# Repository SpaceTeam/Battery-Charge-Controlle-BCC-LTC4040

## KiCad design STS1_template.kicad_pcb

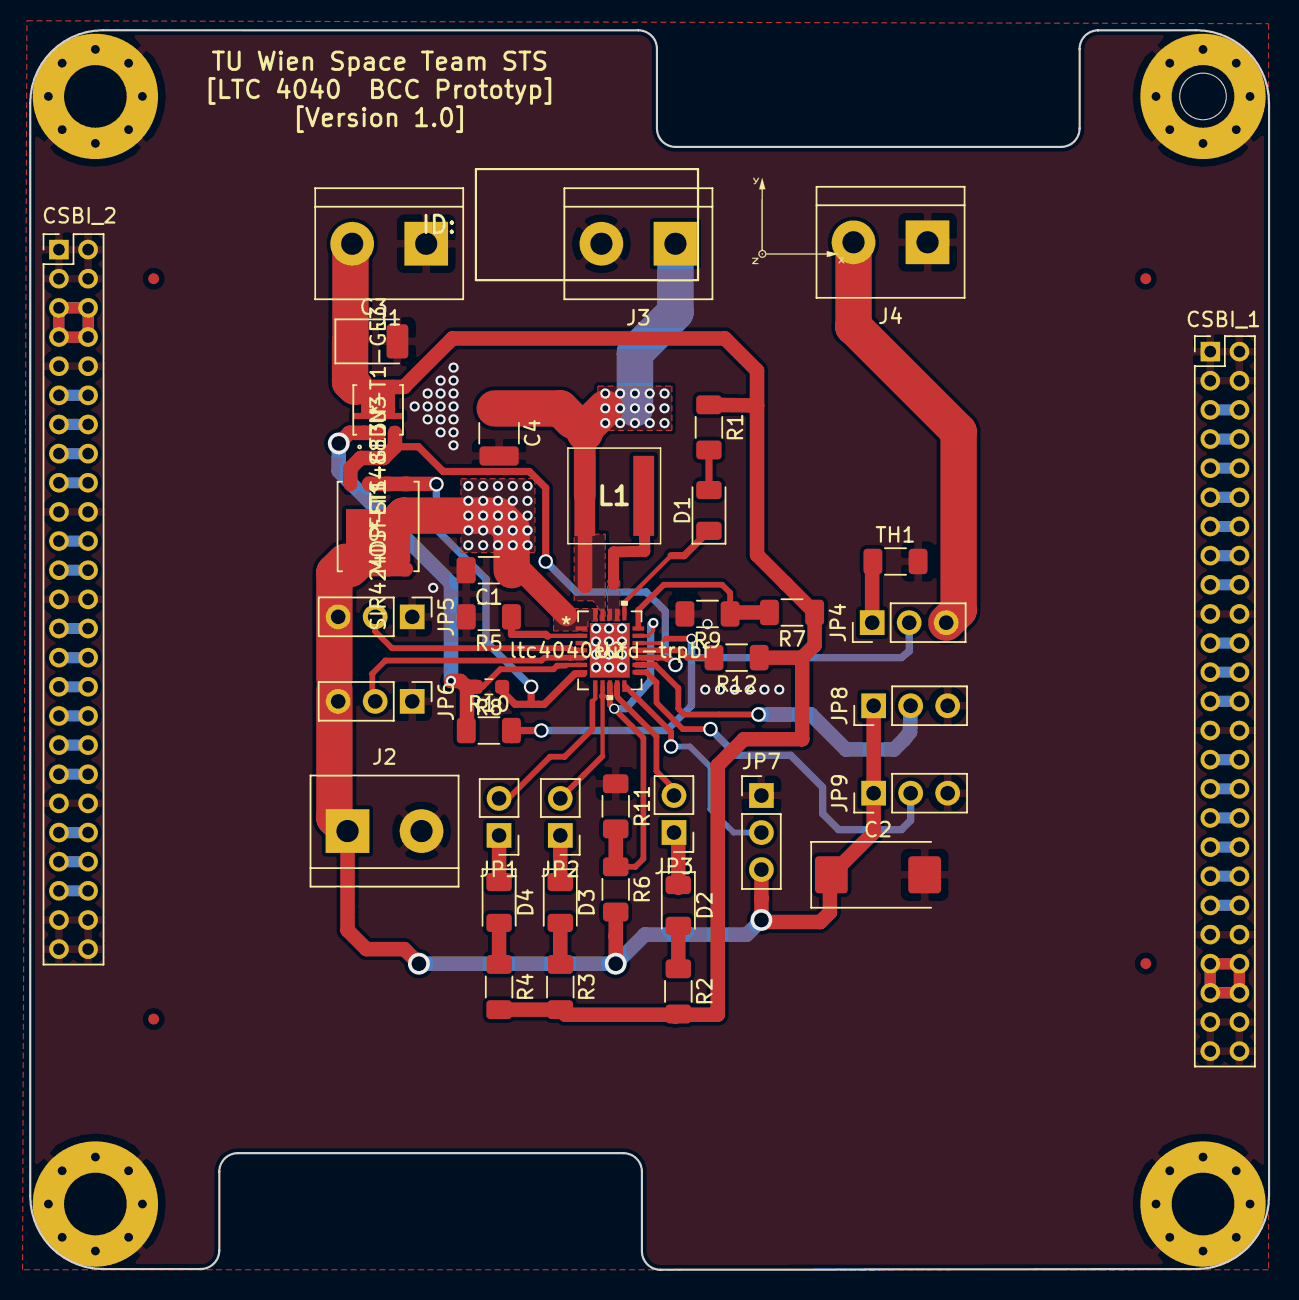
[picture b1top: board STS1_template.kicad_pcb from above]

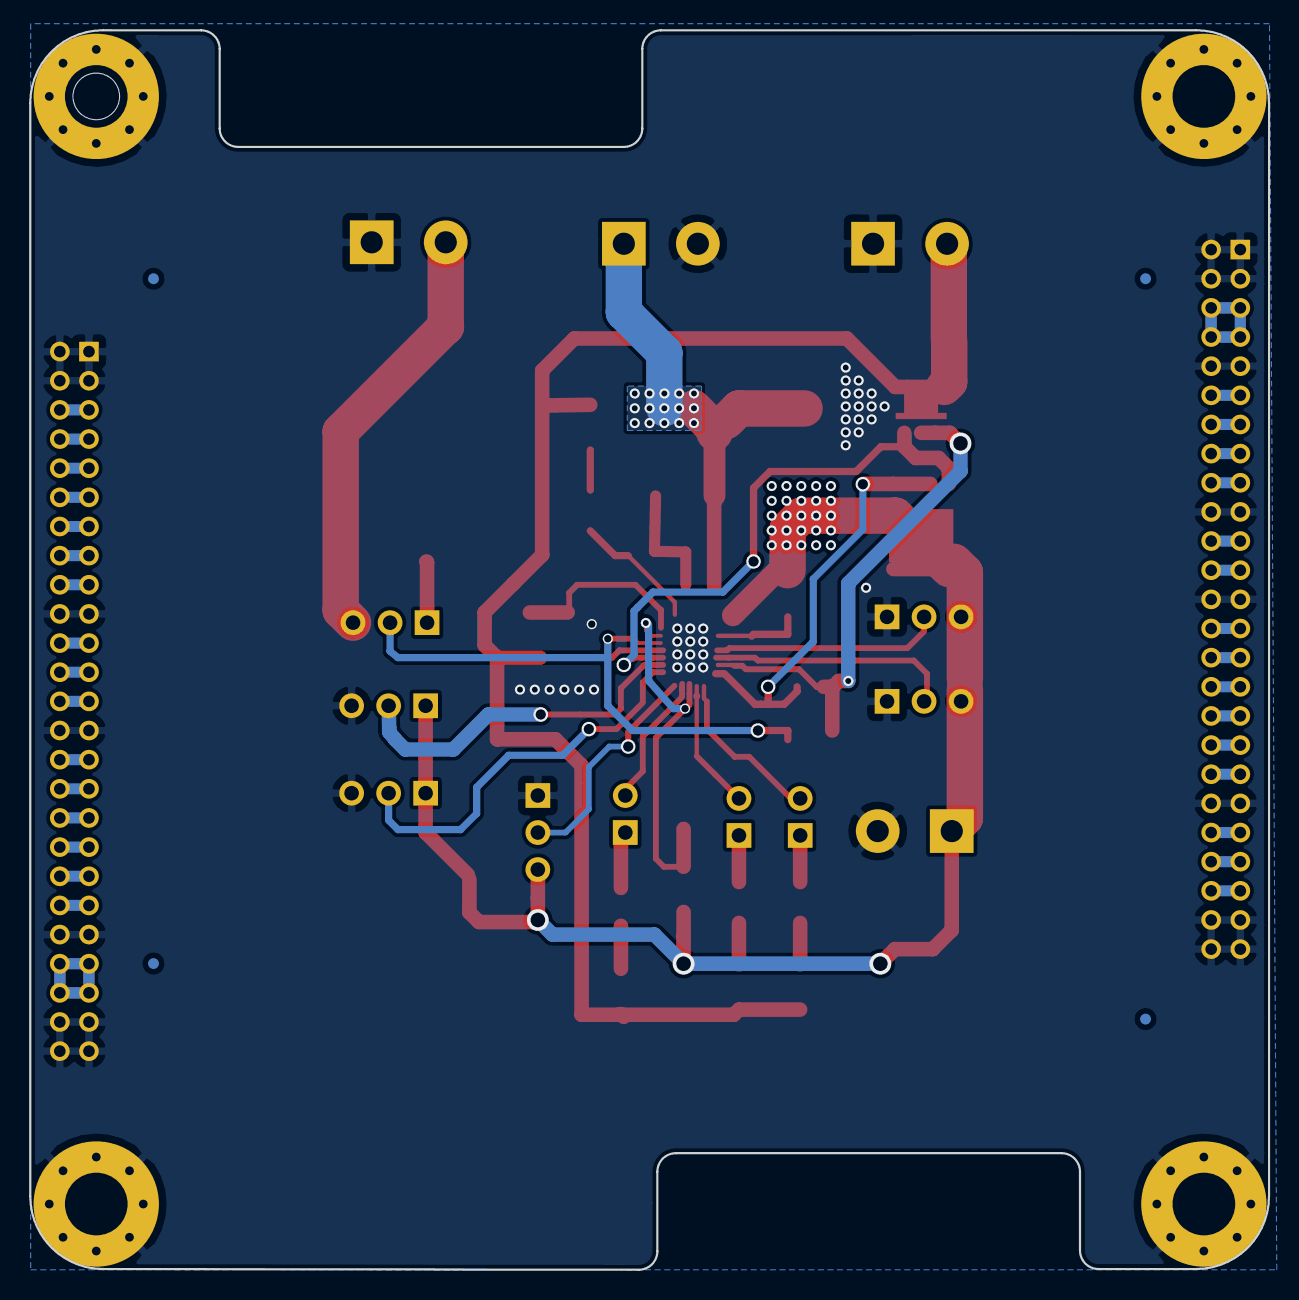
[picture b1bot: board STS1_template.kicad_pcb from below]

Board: 4 copper layers, 85.0 x 85.0 mm, 53 parts (4 on the bottom side), 62 nets.

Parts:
C1: 0,1µF; C_1206_3216Metric_Pad1.33x1.80mm_HandSolder
C2: 100µF; CP_EIA-7343-15_Kemet-W_Pad2.25x2.55mm_HandSolder
C3: 2,2µF; CP_EIA-3528-21_Kemet-B_Pad1.50x2.35mm_HandSolder
C4: 10µF; C_1210_3225Metric_Pad1.33x2.70mm_HandSolder
CSBI_1, CSBI_2: Conn_02x25_Odd_Even; PinHeader_2x25_P2.00mm_Vertical
D1, D2, D3, D4: SMD_LED; LED_1206_3216Metric
FID1, FID2, FID3, FID4, FID5, FID6, FID7, FID8: Fiducial; Fiducial_0.75mm_Mask1.5mm
H1, H2, H3, H4: MountingHole_Pad; MountingHole_4.3mm_M4_Pad_Via
J1: SCC_Eingang; TerminalBlock_bornier-2_P5.08mm
J2: BCC_Ausgang; TerminalBlock_bornier-2_P5.08mm
J3: Battery_Anschluss; TerminalBlock_bornier-2_P5.08mm
J4: Screw_Terminal_01x02; TerminalBlock_bornier-2_P5.08mm
JP1, JP2, JP3: Jumper_2_Bridged; PinHeader_1x02_P2.54mm_Vertical
JP4, JP5, JP6, JP7, JP8, JP9: Jumper_3_Bridged12; PinHeader_1x03_P2.54mm_Vertical
L1: XAL6030-222MEB; XAL6030182MEB
MOSFET1: SIR424DP-T1-GE3
R1, R2, R3, R4: 150; R_1206_3216Metric_Pad1.30x1.75mm_HandSolder
R5: 1,33k; R_1206_3216Metric_Pad1.30x1.75mm_HandSolder
R6: 1700k; R_1206_3216Metric_Pad1.30x1.75mm_HandSolder
R7: 178k; R_1206_3216Metric_Pad1.30x1.75mm_HandSolder
R8: 10m; R_0603_1608Metric_Pad0.98x0.95mm_HandSolder
R9: 60,4k; R_1206_3216Metric_Pad1.30x1.75mm_HandSolder
R10: 10k; R_1206_3216Metric_Pad1.30x1.75mm_HandSolder
R11: 324k; R_1206_3216Metric_Pad1.30x1.75mm_HandSolder
R12: 6,2k; R_1206_3216Metric_Pad1.30x1.75mm_HandSolder
TH1: Thermistor_NTC_10k; R_1206_3216Metric_Pad1.30x1.75mm_HandSolder
U1: coordinate_system; Coordinates
U2: ltc4040eufd-trpbf
U3: SIS488DN-T1-GE3

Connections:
/+5V: C3.1, J1.2, R1.1, R2.2, R3.2, R4.2, R7.1, R12.1, U3.5, U3.6, U3.7, U3.8
/STS1_connector/COBC_SPI_1: CSBI_1.29, CSBI_1.30
/STS1_connector/COBC_SPI_2: CSBI_1.31, CSBI_1.32
/STS1_connector/COBC_SPI_3: CSBI_1.33, CSBI_1.34
/STS1_connector/COBC_SPI_4: CSBI_1.35, CSBI_1.36
/STS1_connector/COBC_SPI_5: CSBI_1.37, CSBI_1.38
/STS1_connector/COBC_SPI_6: CSBI_1.39, CSBI_1.40
/STS1_connector/EDU_EN: CSBI_2.21, CSBI_2.22
/STS1_connector/EDU_Heartbeat: CSBI_2.13, CSBI_2.14
/STS1_connector/EDU_SPI_1: CSBI_2.27, CSBI_2.28
/STS1_connector/EDU_SPI_2: CSBI_2.29, CSBI_2.30
/STS1_connector/EDU_SPI_3: CSBI_2.31, CSBI_2.32
/STS1_connector/EDU_SPI_4: CSBI_2.33, CSBI_2.34
/STS1_connector/EDU_SPI_5: CSBI_2.35, CSBI_2.36
/STS1_connector/EDU_SPI_6: CSBI_2.37, CSBI_2.38
/STS1_connector/EDU_UPDATE: CSBI_2.23, CSBI_2.24
/STS1_connector/EPS_ANT_DEPLOYED: CSBI_1.23, CSBI_1.24
/STS1_connector/EPS_BAT_GOOD: CSBI_1.21, CSBI_1.22
/STS1_connector/EPS_CHARGING: CSBI_1.25, CSBI_1.26
/STS1_connector/UART_COBC_EDU_1: CSBI_2.15, CSBI_2.16
/STS1_connector/UART_COBC_EDU_2: CSBI_2.17, CSBI_2.18
/STS1_connector/UCI_COBC_3V3: CSBI_1.17, CSBI_1.18
/STS1_connector/UCI_COBC_UART_1: CSBI_1.13, CSBI_1.14
/STS1_connector/UCI_COBC_UART_2: CSBI_1.15, CSBI_1.16
/VDD: R8.2, R10.1, U2.6, U3.1, U3.2, U3.3
BAT+: C4.1, J3.1, L1.2, U2.23
GND: C1.2, C2.2, C3.2, C4.2, CSBI_1.1, CSBI_1.2, CSBI_1.3, CSBI_1.4, CSBI_1.19, CSBI_1.20, CSBI_1.27, CSBI_1.28, CSBI_1.41, CSBI_1.42, CSBI_1.47, CSBI_1.48, CSBI_1.49, CSBI_1.50, CSBI_2.1, CSBI_2.2, CSBI_2.3, CSBI_2.4, CSBI_2.9, CSBI_2.10, CSBI_2.19, CSBI_2.20, CSBI_2.25, CSBI_2.26, CSBI_2.39, CSBI_2.40, CSBI_2.47, CSBI_2.48, CSBI_2.49, CSBI_2.50, H1.1, H2.1, H3.1, H4.1, J1.1, J2.2, J3.2, J4.1, JP5.1, JP6.1, JP7.1, JP8.3, JP9.3, R5.2, R9.2, R11.1, TH1.2, U2.25
unnamed: CSBI_1.5, CSBI_1.6
unnamed: CSBI_1.7, CSBI_1.8
unnamed: CSBI_1.9, CSBI_1.10
unnamed: CSBI_1.11, CSBI_1.12
unnamed: CSBI_2.11, CSBI_2.12
unnamed: CSBI_2.41, CSBI_2.42
unnamed: CSBI_2.43, CSBI_2.44
unnamed: CSBI_2.45, CSBI_2.46
unnamed: D1.1, U2.20
unnamed: D1.2, R1.2
unnamed: D2.1, JP3.1
unnamed: D2.2, R2.1
unnamed: D3.1, JP2.1
unnamed: D3.2, R3.1
unnamed: D4.1, JP1.1
unnamed: D4.2, R4.1
unnamed: J4.2, JP4.3
unnamed: JP1.2, U2.8
unnamed: JP2.2, U2.9
unnamed: JP3.2, U2.11
unnamed: JP4.1, TH1.1
unnamed: JP4.2, R10.2, U2.17
unnamed: JP5.2, U2.4
unnamed: JP6.2, U2.5
unnamed: JP7.2, U2.12
unnamed: JP8.2, U2.14
unnamed: JP9.2, U2.13
unnamed: L1.1, U2.21, U2.22
unnamed: MOSFET1.1, MOSFET1.2, MOSFET1.3, R8.1, U2.7
unnamed: MOSFET1.4, U2.15, U3.4
unnamed: R5.1, U2.2
unnamed: R7.2, R9.1, U2.19
unnamed: R6.1, R11.2, U2.10, U2.18
unnamed: R12.2, U2.16
VSS: C1.1, C2.1, CSBI_1.43, CSBI_1.44, CSBI_1.45, CSBI_1.46, CSBI_2.5, CSBI_2.6, CSBI_2.7, CSBI_2.8, J2.1, JP5.3, JP6.3, JP7.3, JP8.1, JP9.1, MOSFET1.5, MOSFET1.6, MOSFET1.7, MOSFET1.8, R6.2, U2.1, U2.24

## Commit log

2021-12-14 Unpacked the zip
2021-12-18 Made some changes to file structure, schematic and PCB - Unzipped the zip - KiCAD libraries should no be imported with relative pathes. - Copper layer IN1 is now connected to GND - Copper layer IN2 i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

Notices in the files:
parts and their libraries:
Copyright 2021 Accelerated Designs. All rights reserved.
